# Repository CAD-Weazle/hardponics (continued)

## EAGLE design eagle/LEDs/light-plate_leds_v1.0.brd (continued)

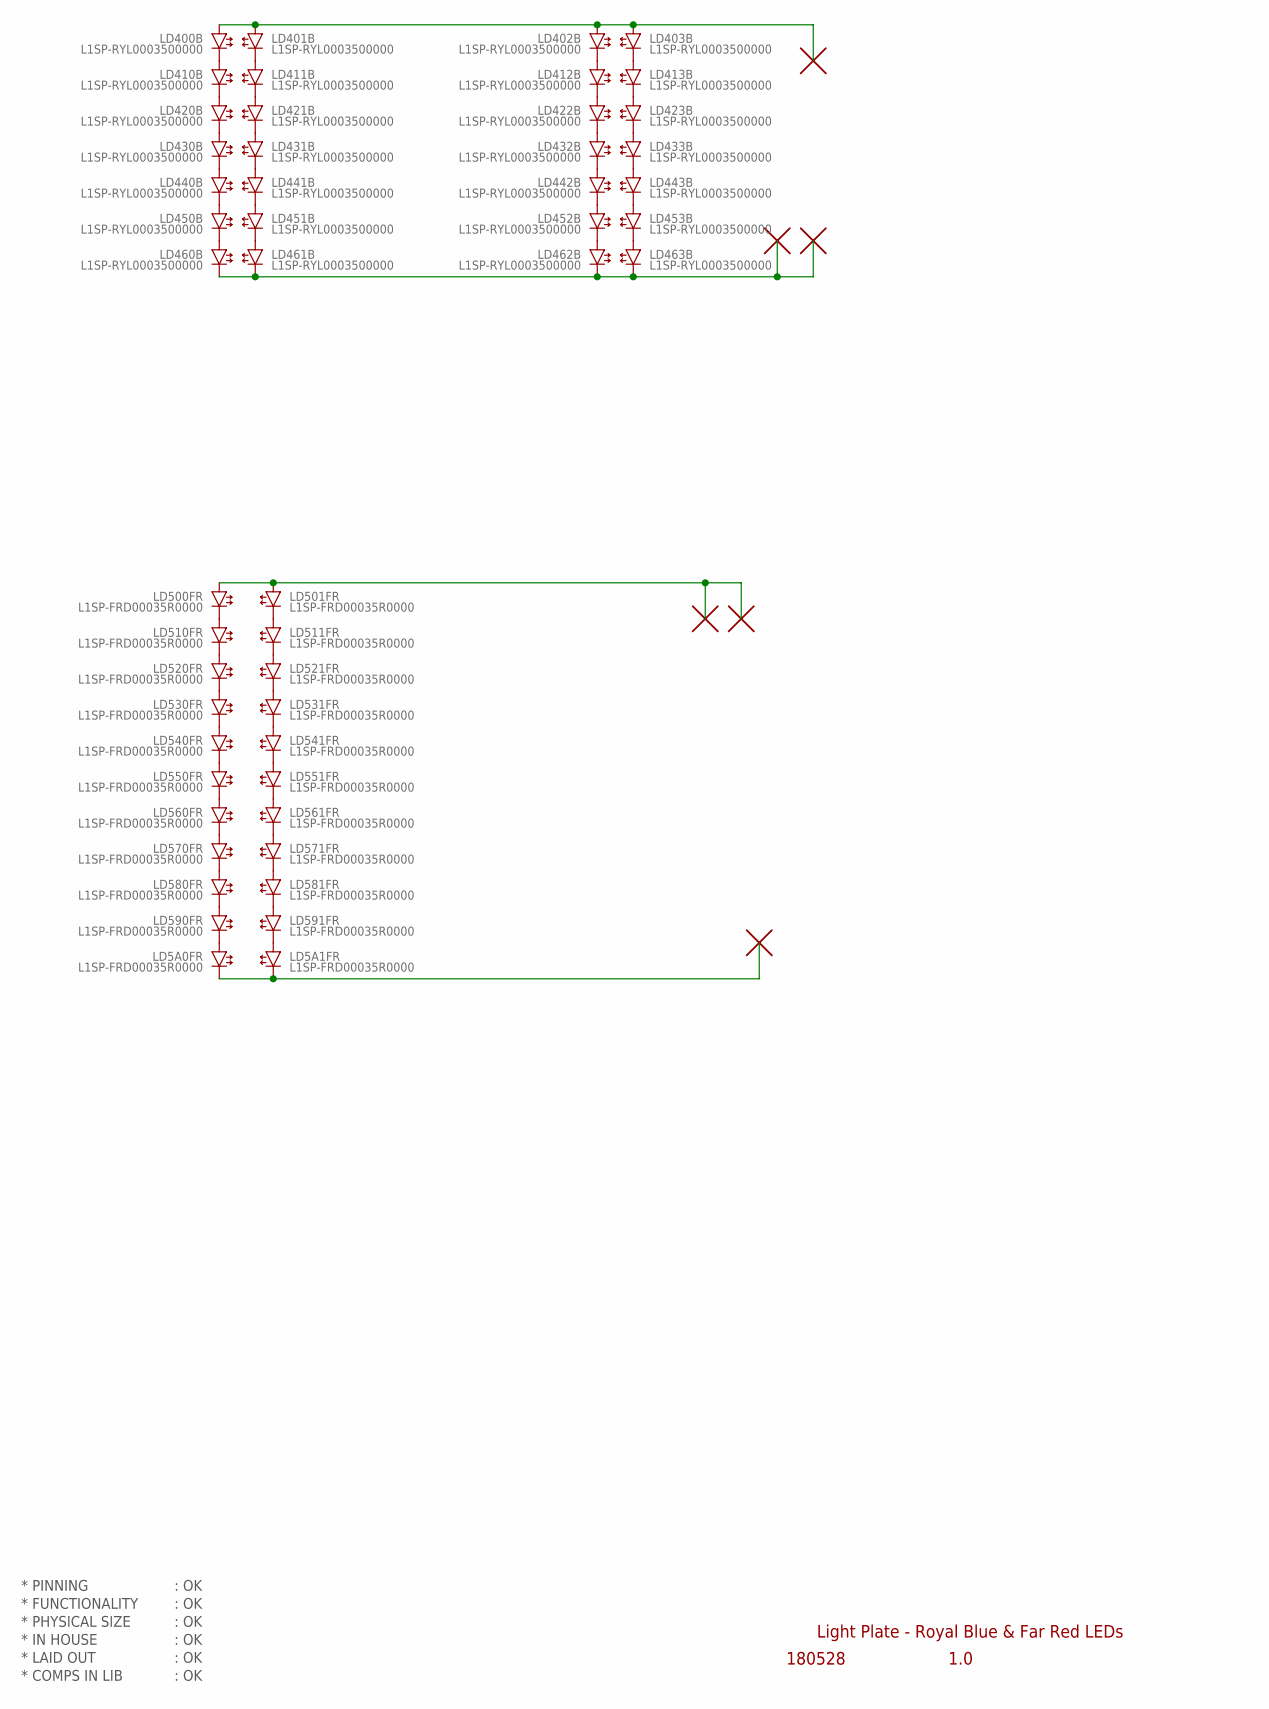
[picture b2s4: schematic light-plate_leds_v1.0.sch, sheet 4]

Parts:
H23, H24, H25, H26, H27, H28: PAD_ROUND_3.2MM
LD5A0FR, LD5A1FR, LD500FR, LD501FR, LD510FR, LD511FR, LD520FR, LD521FR, LD530FR, LD531FR, LD540FR, LD541FR, LD550FR, LD551FR, LD560FR, LD561FR, LD570FR, LD571FR, LD580FR, LD581FR, LD590FR, LD591FR: L1SP-FRD00035R0000; LED_SMD_SUNPLUS35_REVERSED
LD400B, LD401B, LD402B, LD403B, LD410B, LD411B, LD412B, LD413B, LD420B, LD421B, LD422B, LD423B, LD430B, LD431B, LD432B, LD433B, LD440B, LD441B, LD442B, LD443B, LD450B, LD451B, LD452B, LD453B, LD460B, LD461B, LD462B, LD463B: L1SP-RYL0003500000; LED_SMD_SUNPLUS35

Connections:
unnamed: LD402B.C (-), LD412B.A (+)
unnamed: LD412B.C (-), LD422B.A (+)
unnamed: LD422B.C (-), LD432B.A (+)
unnamed: LD432B.C (-), LD442B.A (+)
unnamed: LD442B.C (-), LD452B.A (+)
unnamed: LD452B.C (-), LD462B.A (+)
unnamed: LD403B.C (-), LD413B.A (+)
unnamed: LD413B.C (-), LD423B.A (+)
unnamed: LD423B.C (-), LD433B.A (+)
unnamed: LD433B.C (-), LD443B.A (+)
unnamed: H25.P, H27.P, LD500FR.C (+), LD501FR.C (+)
unnamed: LD443B.C (-), LD453B.A (+)
unnamed: LD453B.C (-), LD463B.A (+)
unnamed: LD400B.C (-), LD410B.A (+)
unnamed: LD410B.C (-), LD420B.A (+)
unnamed: LD420B.C (-), LD430B.A (+)
unnamed: LD430B.C (-), LD440B.A (+)
unnamed: LD440B.C (-), LD450B.A (+)
unnamed: LD450B.C (-), LD460B.A (+)
unnamed: LD401B.C (-), LD411B.A (+)
unnamed: LD411B.C (-), LD421B.A (+)
unnamed: LD421B.C (-), LD431B.A (+)
unnamed: LD431B.C (-), LD441B.A (+)
unnamed: LD441B.C (-), LD451B.A (+)
unnamed: LD451B.C (-), LD461B.A (+)
unnamed: LD500FR.A (-), LD510FR.C (+)
unnamed: LD510FR.A (-), LD520FR.C (+)
unnamed: LD520FR.A (-), LD530FR.C (+)
unnamed: LD530FR.A (-), LD540FR.C (+)
unnamed: LD540FR.A (-), LD550FR.C (+)
unnamed: LD550FR.A (-), LD560FR.C (+)
unnamed: LD560FR.A (-), LD570FR.C (+)
unnamed: LD570FR.A (-), LD580FR.C (+)
unnamed: LD580FR.A (-), LD590FR.C (+)
unnamed: LD5A0FR.C (+), LD590FR.A (-)
unnamed: LD501FR.A (-), LD511FR.C (+)
unnamed: LD511FR.A (-), LD521FR.C (+)
unnamed: LD521FR.A (-), LD531FR.C (+)
unnamed: LD531FR.A (-), LD541FR.C (+)
unnamed: LD541FR.A (-), LD551FR.C (+)
unnamed: LD551FR.A (-), LD561FR.C (+)
unnamed: LD561FR.A (-), LD571FR.C (+)
unnamed: LD571FR.A (-), LD581FR.C (+)
unnamed: LD581FR.A (-), LD591FR.C (+)
unnamed: LD5A1FR.C (+), LD591FR.A (-)
unnamed: H24.P, H28.P, LD460B.C (-), LD461B.C (-), LD462B.C (-), LD463B.C (-)
unnamed: H23.P, LD400B.A (+), LD401B.A (+), LD402B.A (+), LD403B.A (+)
unnamed: H26.P, LD5A0FR.A (-), LD5A1FR.A (-)

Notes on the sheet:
* PINNING
* FUNCTIONALITY
* PHYSICAL SIZE
* LAID OUT
* COMPS IN LIB
* IN HOUSE
: OK
Light Plate - Royal Blue & Far Red LEDs
1.0
180528

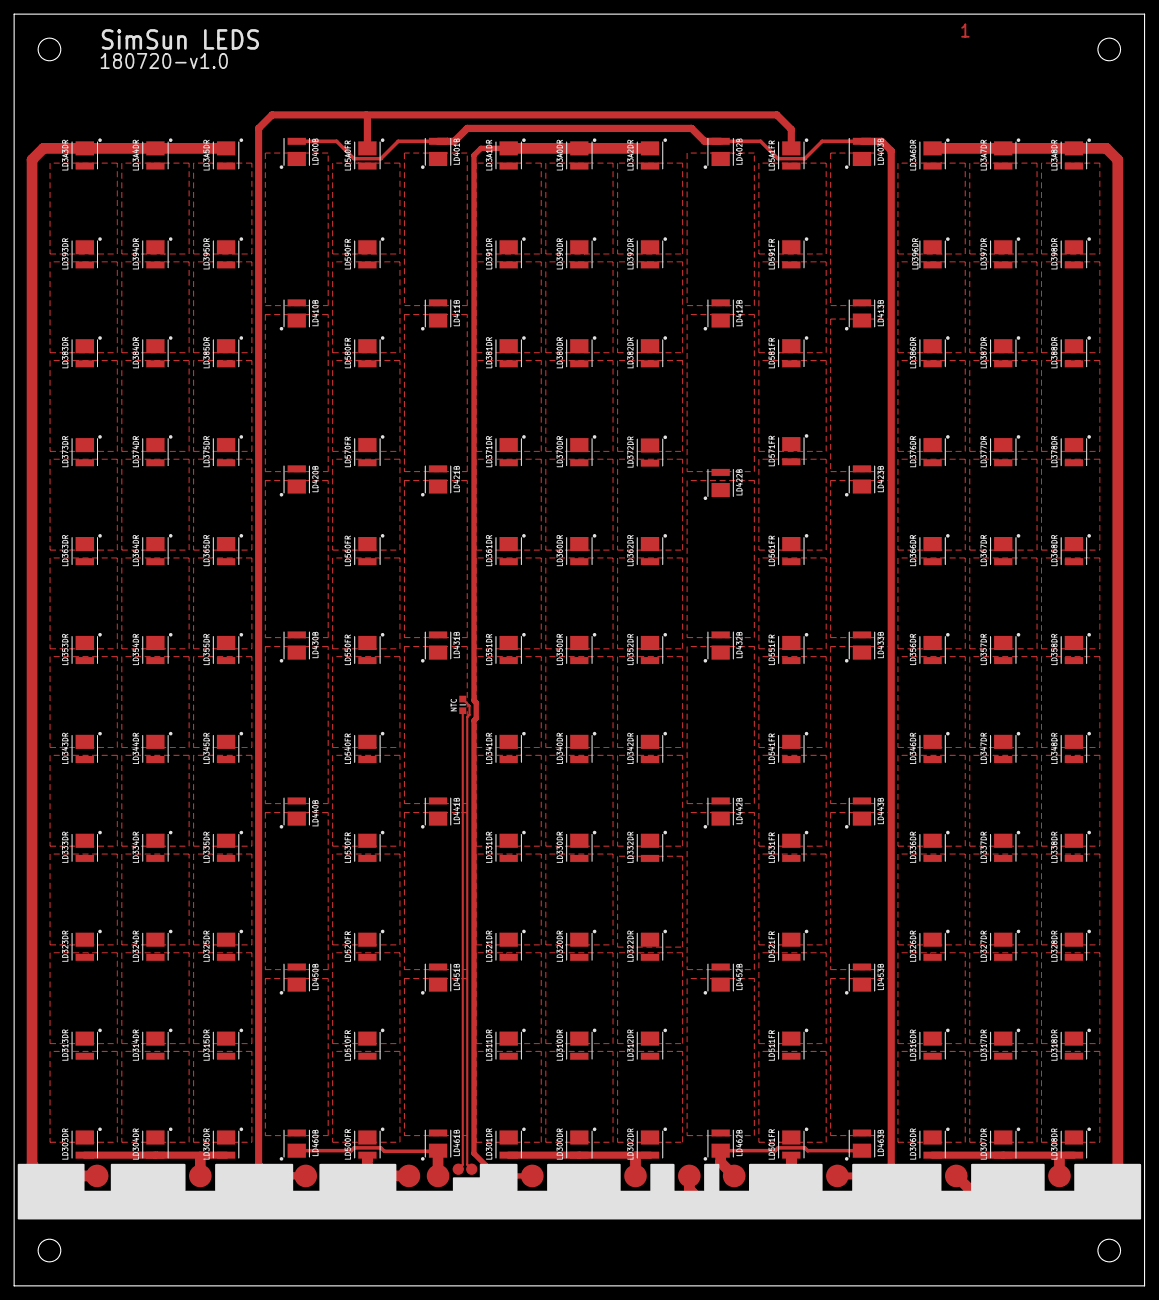
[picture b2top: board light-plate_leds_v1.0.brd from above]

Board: 2 copper layers, 160.0 x 180.0 mm, 168 parts (0 on the bottom side), 146 nets.

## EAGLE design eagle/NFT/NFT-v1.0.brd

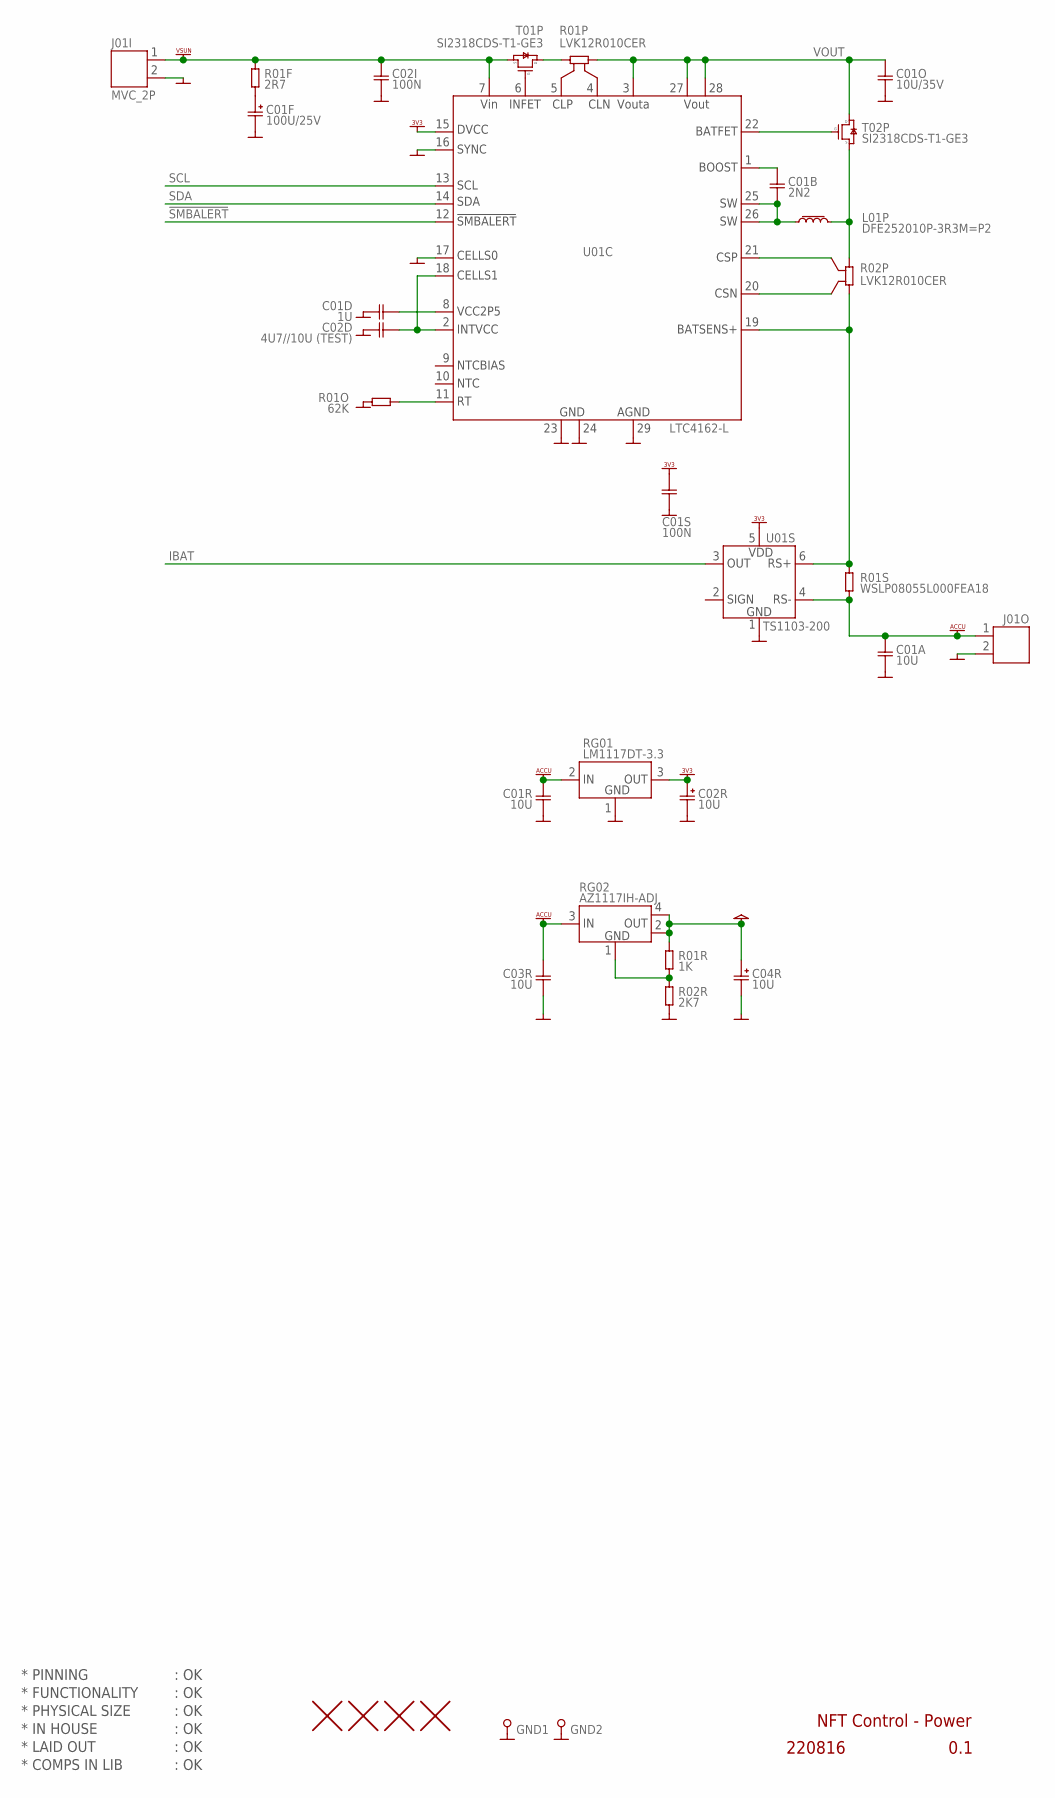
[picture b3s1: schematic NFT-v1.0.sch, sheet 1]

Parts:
C01A: 10U; CAP0805
C01B: 2N2; CAP0402
C01D: 1U; CAP0402
C01F: 100U/25V; ECAP_SMD
C01O: 10U/35V; CAP0805
C01R, C03R: 10U; CAP0603
C01S, C02I: 100N; CAP0402
C02D: 4U7//10U (TEST); CAP0402
C02R, C04R: 10U; ECAP_SMA
GND1, GND2: PIN_TEST; HOLE_PTH_0.8MM
H1, H2, H3, H4: HOLE_NPTH_3.2MM
J01I: MVC_2P; CON_PHOENIX_COMBICON_MCV_HEADER_P
J01O: CON_PHOENIX_COMBICON_MCV_HEADER_2P; CON_PHOENIX_COMBICON_MCV_HEADER_P
L01P: DFE252010P-3R3M=P2; L_1008
R01F: 2R7; RES0603
R01O: 62K; RES0402
R01P, R02P: LVK12R010CER; RES1206_LVK12R010CER
R01R: 1K; RES0402
R01S: WSLP08055L000FEA18; RES0805
R02R: 2K7; RES0402
RG01: LM1117DT-3.3; TO252
RG02: AZ1117IH-ADJ; SOT223
T01P, T02P: SI2318CDS-T1-GE3; NFET_SOT23
U01C: LTC4162-L; QFN28_4X5
U01S: TS1103-200; SOT23-6

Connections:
!SMBALERT: U01C.12 (12.!SMBALERT); also elsewhere on the board
ACCU: C01A.1, C01R.1, C03R.1, J01O.1, R01S.2, RG01.2 (2.IN), RG02.3 (3.IN), U01S.4 (4.RS-); also elsewhere on the board
BATFET: T02P.G (G1), U01C.22 (22.BATFET)
BOOST: C01B.1, U01C.1 (1.BOOST)
CHARGER_OUT: R01S.1, R02P.1, U01C.19 (19.BATSENS+), U01S.6 (6.RS+)
CLN: R01P.4, U01C.4 (4.CLN)
CLP: R01P.3, U01C.5 (5.CLP)
CSN: R02P.3, U01C.20 (20.CSN)
CSP: R02P.4, U01C.21 (21.CSP)
FB1: R01R.2, R02R.1, RG02.1 (1.GND)
GND: C01A.2, C01D.1, C01F.-, C01O.2, C01R.2, C01S.2, C02D.1, C02I.2, C02R.-, C03R.2, C04R.-, GND1.1, GND2.1, J01I.2, J01O.2, R01O.1, R02R.2, RG01.1 (1.GND), U01C.16 (16.SYNC), U01C.17 (17.CELLS0), U01C.23 (23.GND), U01C.24 (24.GND), U01C.29 (29.AGND), U01C.V1 (29.AGND), U01C.V2 (29.AGND), U01C.V3 (29.AGND), U01C.V4 (29.AGND), U01S.1 (1.GND); also elsewhere on the board
IBAT: U01S.3 (3.OUT); also elsewhere on the board
INFET: T01P.G (G1), U01C.6 (6.INFET)
INTVCC: C02D.2, U01C.2 (2.INTVCC), U01C.18 (18.CELLS1)
unnamed: C01F.+, R01F.2
unnamed: R01P.1, T01P.D (D3)
unnamed: L01P.2, R02P.2, T02P.S (S2)
RT: R01O.2, U01C.11 (11.RT)
SCL: U01C.13 (13.SCL); also elsewhere on the board
SDA: U01C.14 (14.SDA); also elsewhere on the board
SW: C01B.2, L01P.1, U01C.25 (25.SW), U01C.26 (26.SW)
VCC: C04R.+, R01R.1, RG02.2 (2.OUT), RG02.4 (4.OUT); also elsewhere on the board
VCC2P5: C01D.2, U01C.8 (8.VCC2P5)
VDD_3V3: C01S.1, C02R.+, RG01.3 (3.OUT), U01C.15 (15.DVCC), U01S.5 (5.VDD); also elsewhere on the board
VOUT: C01O.1, R01P.2, T02P.D (D3), U01C.3 (3.VOUTA), U01C.27 (27.VOUT), U01C.28 (28.VOUT)
VSUN: C02I.1, J01I.1, R01F.1, T01P.S (S2), U01C.7 (7.VIN)

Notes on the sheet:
* PINNING
* FUNCTIONALITY
* PHYSICAL SIZE
* LAID OUT
* COMPS IN LIB
* IN HOUSE
NFT Control - Power
220816
0.1
: OK

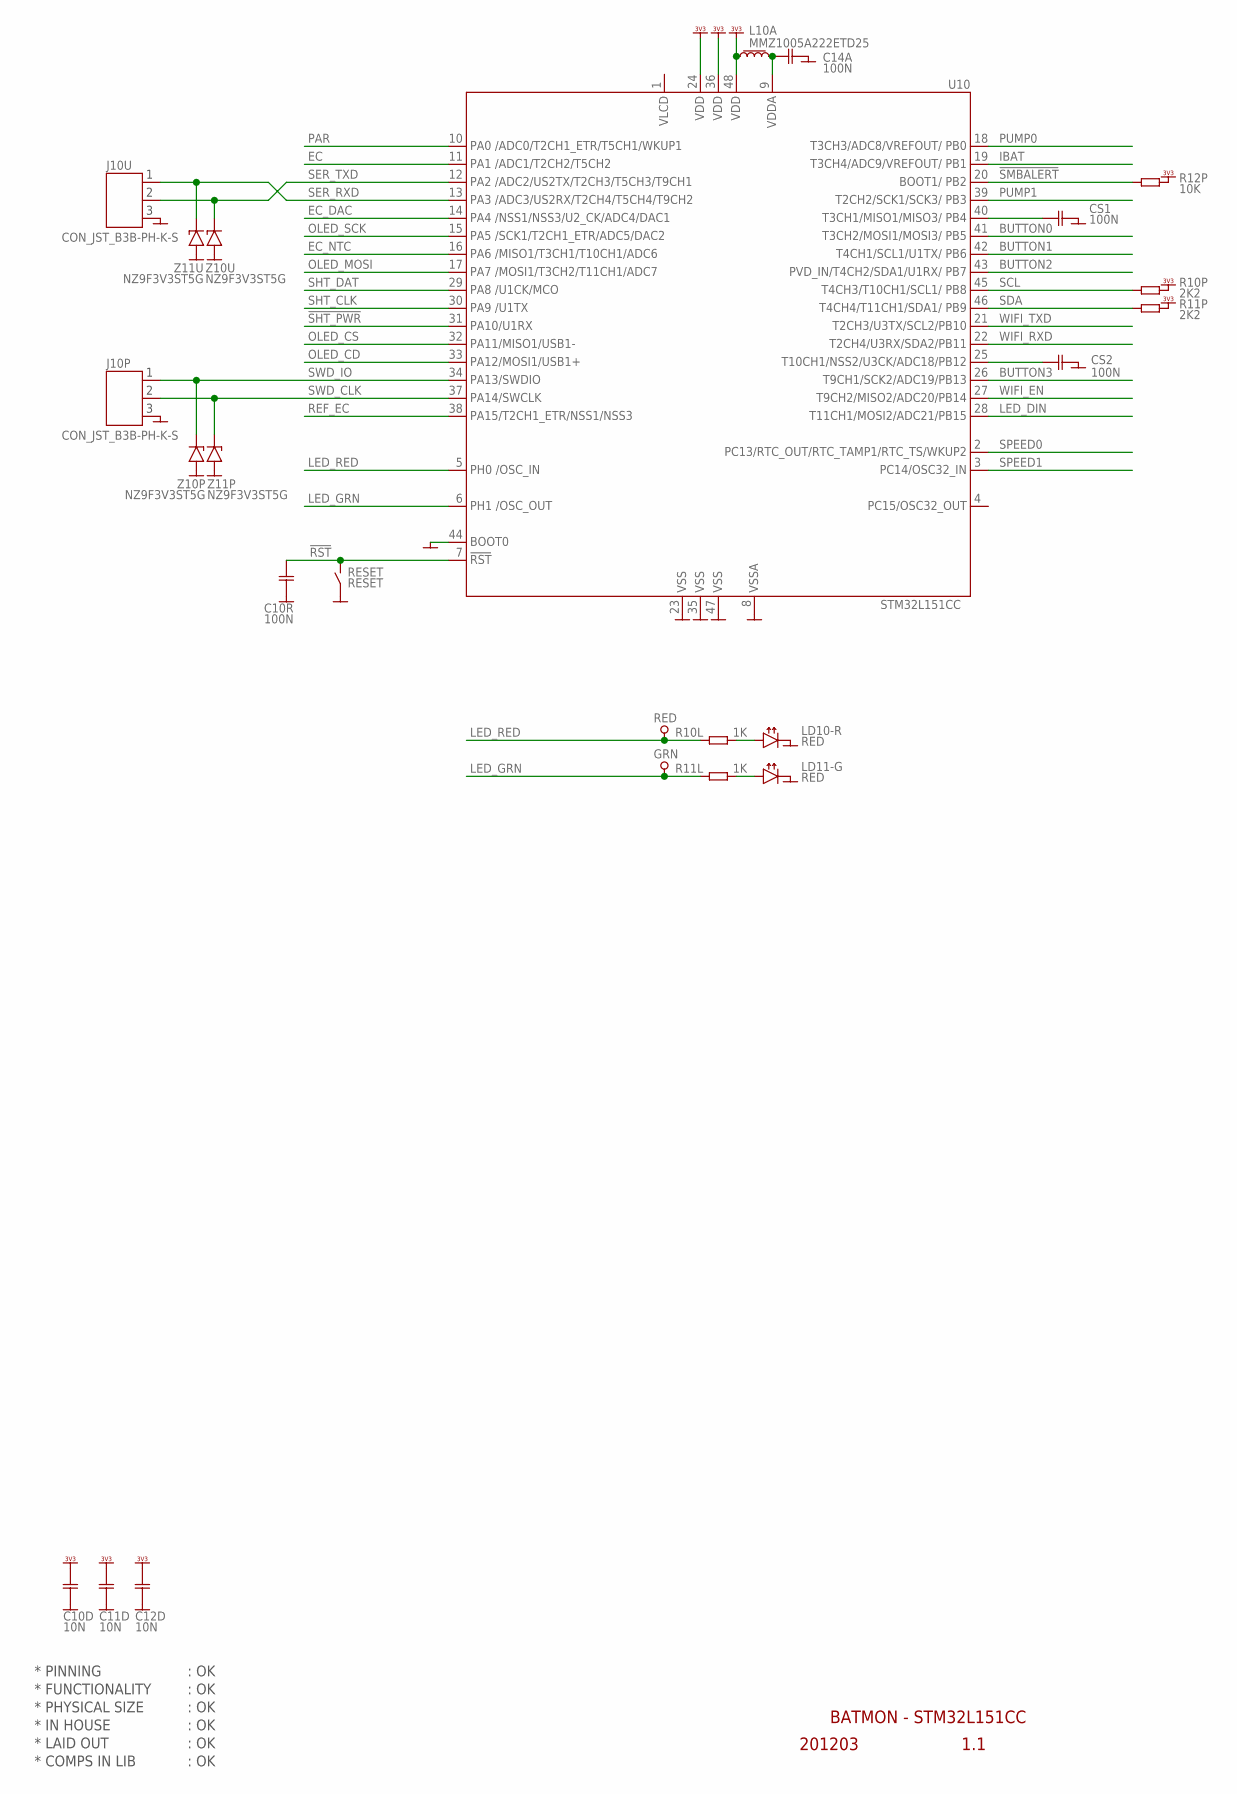
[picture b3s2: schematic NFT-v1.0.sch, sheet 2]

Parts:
C10D, C11D, C12D: 10N; CAP0402
C10R, C14A: 100N; CAP0402
CS1, CS2: 100N; CAP0402
GRN: PIN_TEST_0.6MM; HOLE_PTH_0.6MM
J10P, J10U: CON_JST_B3B-PH-K-S
L10A: MMZ1005A222ETD25; L_0402
LD10-R, LD11-G: RED; LED_SMD_0402
R10L, R11L: 1K; RES0402
R10P, R11P: 2K2; RES0402
R12P: 10K; RES0402
RED: PIN_TEST_0.6MM; HOLE_PTH_0.6MM
RESET: RESET; SWITCH_SMD_PBUTTON_2P
U10: STM32L151CC; LQFP48
Z10P, Z10U, Z11P, Z11U: NZ9F3V3ST5G; ZENER_SOD923

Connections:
!RST: C10R.1, RESET.1 (1-2), U10.7 (7.!RST)
!SHT_PWR: U10.31 (31.PA10); also elsewhere on the board
!SMBALERT: R12P.1, U10.20 (20.PB2); also elsewhere on the board
BUTTON0: U10.41 (41.PB5); also elsewhere on the board
BUTTON1: U10.42 (42.PB6); also elsewhere on the board
BUTTON2: U10.43 (43.PB7); also elsewhere on the board
BUTTON3: U10.26 (26.PB13); also elsewhere on the board
CSAMPLE: CS1.1, U10.40 (40.PB4)
CSAMPLE1: CS2.1, U10.25 (25.PB12)
EC: U10.11 (11.PA1); also elsewhere on the board
EC_DAC: U10.14 (14.PA4); also elsewhere on the board
EC_NTC: U10.16 (16.PA6); also elsewhere on the board
GND: C10D.2, C10R.2, C11D.2, C12D.2, C14A.2, CS1.2, CS2.2, J10P.3, J10U.3, LD10-R.C, LD11-G.C, RESET.2 (3-4), U10.8 (8.GND), U10.23 (23.GND), U10.35 (35.GND), U10.44 (44.BOOT0), U10.47 (47.GND), Z10P.2 (A), Z10U.2 (A), Z11P.2 (A), Z11U.2 (A); also elsewhere on the board
IBAT: U10.19 (19.PB1); also elsewhere on the board
LED_DIN: U10.28 (28.PB15); also elsewhere on the board
LED_GRN: GRN.1, R11L.1, U10.6 (6.OSC_OUT)
LED_RED: R10L.1, RED.1, U10.5 (5.OSC_IN)
unnamed: LD11-G.A, R11L.2
unnamed: LD10-R.A, R10L.2
OLED_CD: U10.33 (33.PA12); also elsewhere on the board
OLED_CS: U10.32 (32.PA11); also elsewhere on the board
OLED_MOSI: U10.17 (17.PA7); also elsewhere on the board
OLED_SCK: U10.15 (15.PA5); also elsewhere on the board
PAR: U10.10 (10.PA0); also elsewhere on the board
PUMP0: U10.18 (18.PB0); also elsewhere on the board
PUMP1: U10.39 (39.PB3); also elsewhere on the board
REF_EC: U10.38 (38.PA15); also elsewhere on the board
SCL: R10P.1, U10.45 (45.PB8); also elsewhere on the board
SDA: R11P.1, U10.46 (46.PB9); also elsewhere on the board
SER_RXD: J10U.1, U10.13 (13.PA3), Z11U.1 (C)
SER_TXD: J10U.2, U10.12 (12.PA2), Z10U.1 (C)
SHT_CLK: U10.30 (30.PA9); also elsewhere on the board
SHT_DAT: U10.29 (29.PA8); also elsewhere on the board
SPEED0: U10.2 (2.PC13); also elsewhere on the board
SPEED1: U10.3 (3.PC14); also elsewhere on the board
SWD_CLK: J10P.2, U10.37 (37.PA14), Z11P.1 (C)
SWD_IO: J10P.1, U10.34 (34.PA13), Z10P.1 (C)
VDDA: C14A.1, L10A.2, U10.9 (9.VDD)
VDD_3V3: C10D.1, C11D.1, C12D.1, L10A.1, R10P.2, R11P.2, R12P.2, U10.24 (24.VDD), U10.36 (36.VDD), U10.48 (48.VDD); also elsewhere on the board
WIFI_EN: U10.27 (27.PB14); also elsewhere on the board
WIFI_RXD: U10.22 (22.PB11); also elsewhere on the board
WIFI_TXD: U10.21 (21.PB10); also elsewhere on the board

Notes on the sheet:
* PINNING
* FUNCTIONALITY
* PHYSICAL SIZE
* LAID OUT
* COMPS IN LIB
* IN HOUSE
: OK
BATMON - STM32L151CC
201203
1.1

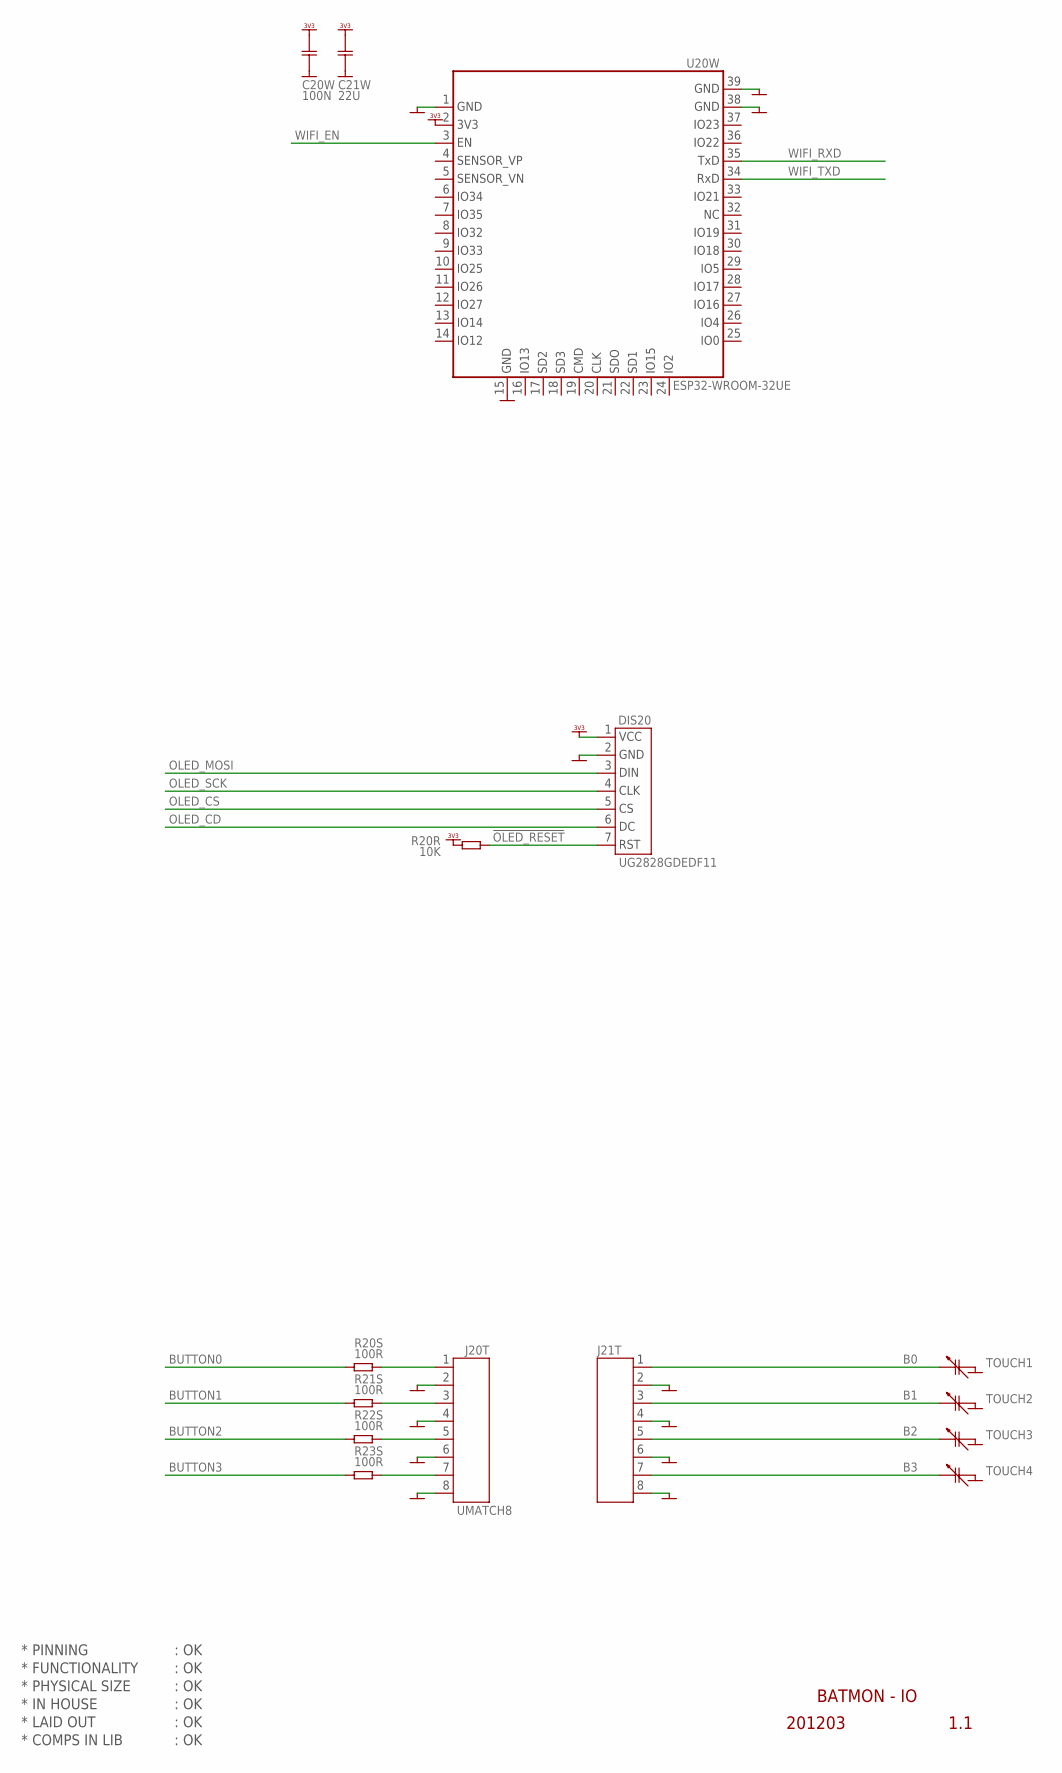
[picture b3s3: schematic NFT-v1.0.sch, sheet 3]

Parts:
C20W: 100N; CAP0402
C21W: 22U; CAP0805
DIS20: UG2828GDEDF11; WAVESHARE_1.5"OLED128X128
J20T: UMATCH8; CON_MICROMATCH_TOP_8F
J21T: CON_MICROMATCH_8F_SMD-TOP; CON_MICROMATCH_TOP_8F_SMD
R20R: 10K; RES0402
R20S, R21S, R22S, R23S: 100R; RES0402
TOUCH1, TOUCH2, TOUCH3, TOUCH4: CAP_TOUCH_ROUND_10MM_SINGLE
U20W: ESP32-WROOM-32UE

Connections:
!OLED_RESET: DIS20.7 (7.RST), R20R.2
B0: J20T.1, J21T.1, R20S.2, TOUCH1.1
B1: J20T.3, J21T.3, R21S.2, TOUCH2.1
B2: J20T.5, J21T.5, R22S.2, TOUCH3.1
B3: J20T.7, J21T.7, R23S.2, TOUCH4.1
BUTTON0: R20S.1; also elsewhere on the board
BUTTON1: R21S.1; also elsewhere on the board
BUTTON2: R22S.1; also elsewhere on the board
BUTTON3: R23S.1; also elsewhere on the board
GND: C20W.2, C21W.2, DIS20.2 (2.GND), J20T.2, J20T.4, J20T.6, J20T.8, J21T.2, J21T.4, J21T.6, J21T.8, TOUCH1.2, TOUCH2.2, TOUCH3.2, TOUCH4.2, U20W.1 (1.GND), U20W.15 (15.GND), U20W.38 (38.GND), U20W.GND (39.GND); also elsewhere on the board
OLED_CD: DIS20.6 (6.DC); also elsewhere on the board
OLED_CS: DIS20.5 (5.CS); also elsewhere on the board
OLED_MOSI: DIS20.3 (3.DIN); also elsewhere on the board
OLED_SCK: DIS20.4 (4.CLK); also elsewhere on the board
VDD_3V3: C20W.1, C21W.1, DIS20.1 (1.VCC), R20R.1, U20W.2 (2.3V3); also elsewhere on the board
WIFI_EN: U20W.3 (3.EN); also elsewhere on the board
WIFI_RXD: U20W.35 (35.TXD0); also elsewhere on the board
WIFI_TXD: U20W.34 (34.RXD0); also elsewhere on the board

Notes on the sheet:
* PINNING
* FUNCTIONALITY
* PHYSICAL SIZE
* LAID OUT
* COMPS IN LIB
* IN HOUSE
BATMON - IO
201203
1.1
: OK

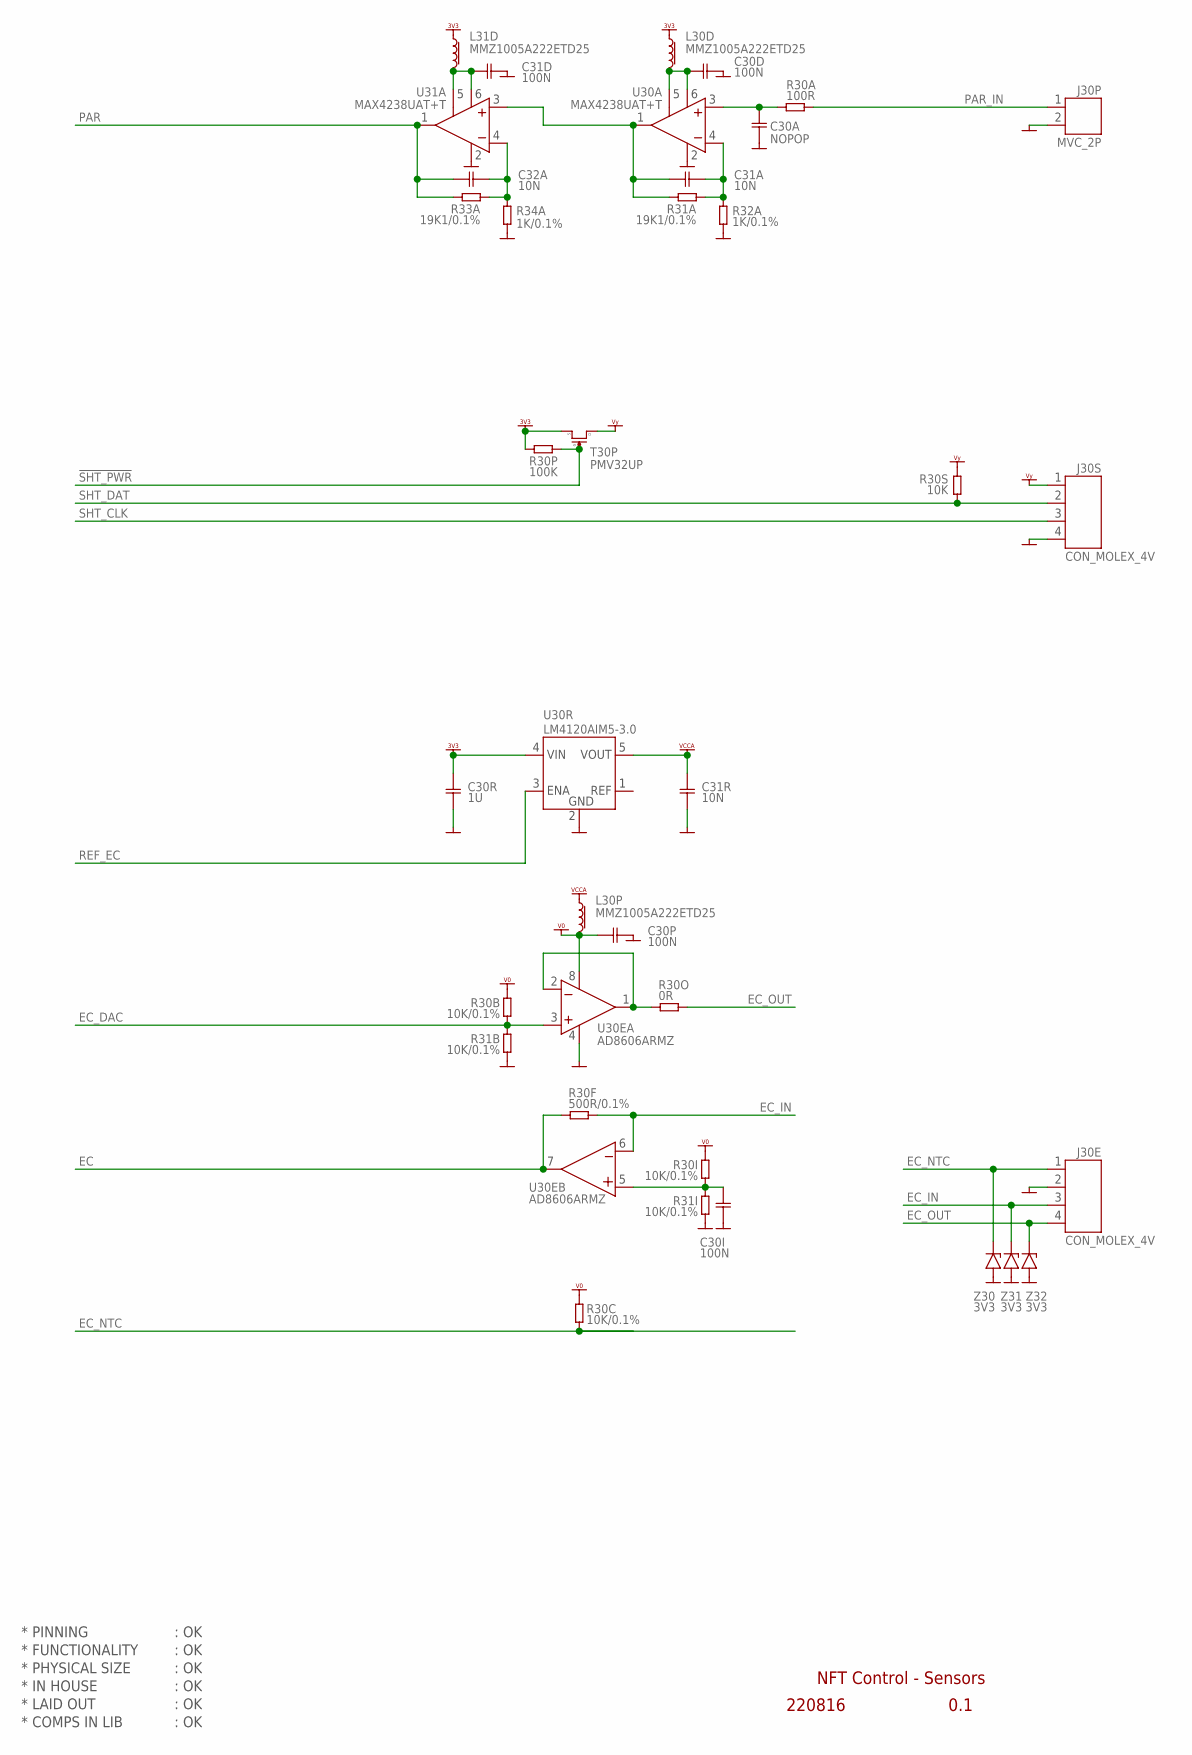
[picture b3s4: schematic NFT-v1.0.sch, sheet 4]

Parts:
C30A: NOPOP; CAP0402
C30D, C30I, C30P, C31D: 100N; CAP0402
C30R: 1U; CAP0402
C31A, C31R, C32A: 10N; CAP0402
J30E, J30S: CON_MOLEX_4V
J30P: MVC_2P; CON_PHOENIX_COMBICON_MCV_HEADER_P
L30D, L30P, L31D: MMZ1005A222ETD25; L_0402
R30A: 100R; RES0402
R30B, R30C, R30I, R31B, R31I: 10K/0.1%; RES0402
R30F: 500R/0.1%; RES0402
R30O: 0R; RES0402
R30P: 100K; RES0402
R30S: 10K; RES0402
R31A, R33A: 19K1/0.1%; RES0402
R32A, R34A: 1K/0.1%; RES0402
T30P: PMV32UP; PFET_SOT23
U30A, U31A: MAX4238UAT+T; SOT23-6
U30E: AD8606ARMZ; MSOP8
U30R: LM4120AIM5-3.0; SOT23-5
Z30, Z31, Z32: 3V3; ZENER_SOD80

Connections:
!SHT_PWR: R30P.2, T30P.1 (G); also elsewhere on the board
EC: R30F.2, U30E.7 (7.OUT); also elsewhere on the board
EC30_BUF: R30O.2, U30E.1 (1.OUT), U30E.2 (2.IN-)
EC_DAC: R30B.2, R31B.1, U30E.3 (3.IN+); also elsewhere on the board
EC_IN: J30E.3, R30F.1, U30E.6 (6.IN-), Z31.2 (C)
EC_NTC: J30E.1, R30C.2, Z30.2 (C); also elsewhere on the board
EC_OUT: J30E.4, R30O.1, Z32.2 (C)
GND: C30A.1, C30D.2, C30I.1, C30P.2, C30R.2, C31D.2, C31R.2, J30E.2, J30P.2, J30S.4, R31B.2, R31I.2, R32A.2, R34A.2, U30A.2 (2.V-), U30E.4 (4.V-), U30R.2 (2.GND), U31A.2 (2.V-), Z30.1 (A), Z31.1 (A), Z32.1 (A); also elsewhere on the board
IMUXF: C30A.2, R30A.2, U30A.3 (3.IN+)
unnamed: C31D.1, L31D.2, U31A.5 (5.!SHDN), U31A.6 (6.V+)
unnamed: C30I.2, R30I.2, R31I.1, U30E.5 (5.IN+)
unnamed: C30D.1, L30D.2, U30A.5 (5.!SHDN), U30A.6 (6.V+)
unnamed: C32A.2, R33A.1, R34A.1, U31A.4 (4.IN-)
unnamed: C31A.1, R31A.2, U30A.1 (1.OUT), U31A.3 (3.IN+)
unnamed: C31A.2, R31A.1, R32A.1, U30A.4 (4.IN-)
PAR: C32A.1, R33A.2, U31A.1 (1.OUT); also elsewhere on the board
PAR_IN: J30P.1, R30A.1
REF_EC: U30R.3 (3.ENA); also elsewhere on the board
SHT_CLK: J30S.3; also elsewhere on the board
SHT_DAT: J30S.2, R30S.2; also elsewhere on the board
V0: C30P.1, L30P.2, R30B.1, R30C.1, R30I.1, U30E.8 (8.V+)
VCCA: C31R.1, L30P.1, U30R.5 (5.VOUT)
VDD_3V3: C30R.1, L30D.1, L31D.1, R30P.1, T30P.2 (S), U30R.4 (4.VIN); also elsewhere on the board
VY: J30S.1, R30S.1, T30P.3 (D)

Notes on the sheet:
* PINNING
* FUNCTIONALITY
* PHYSICAL SIZE
* LAID OUT
* COMPS IN LIB
* IN HOUSE
NFT Control - Sensors
220816
0.1
: OK

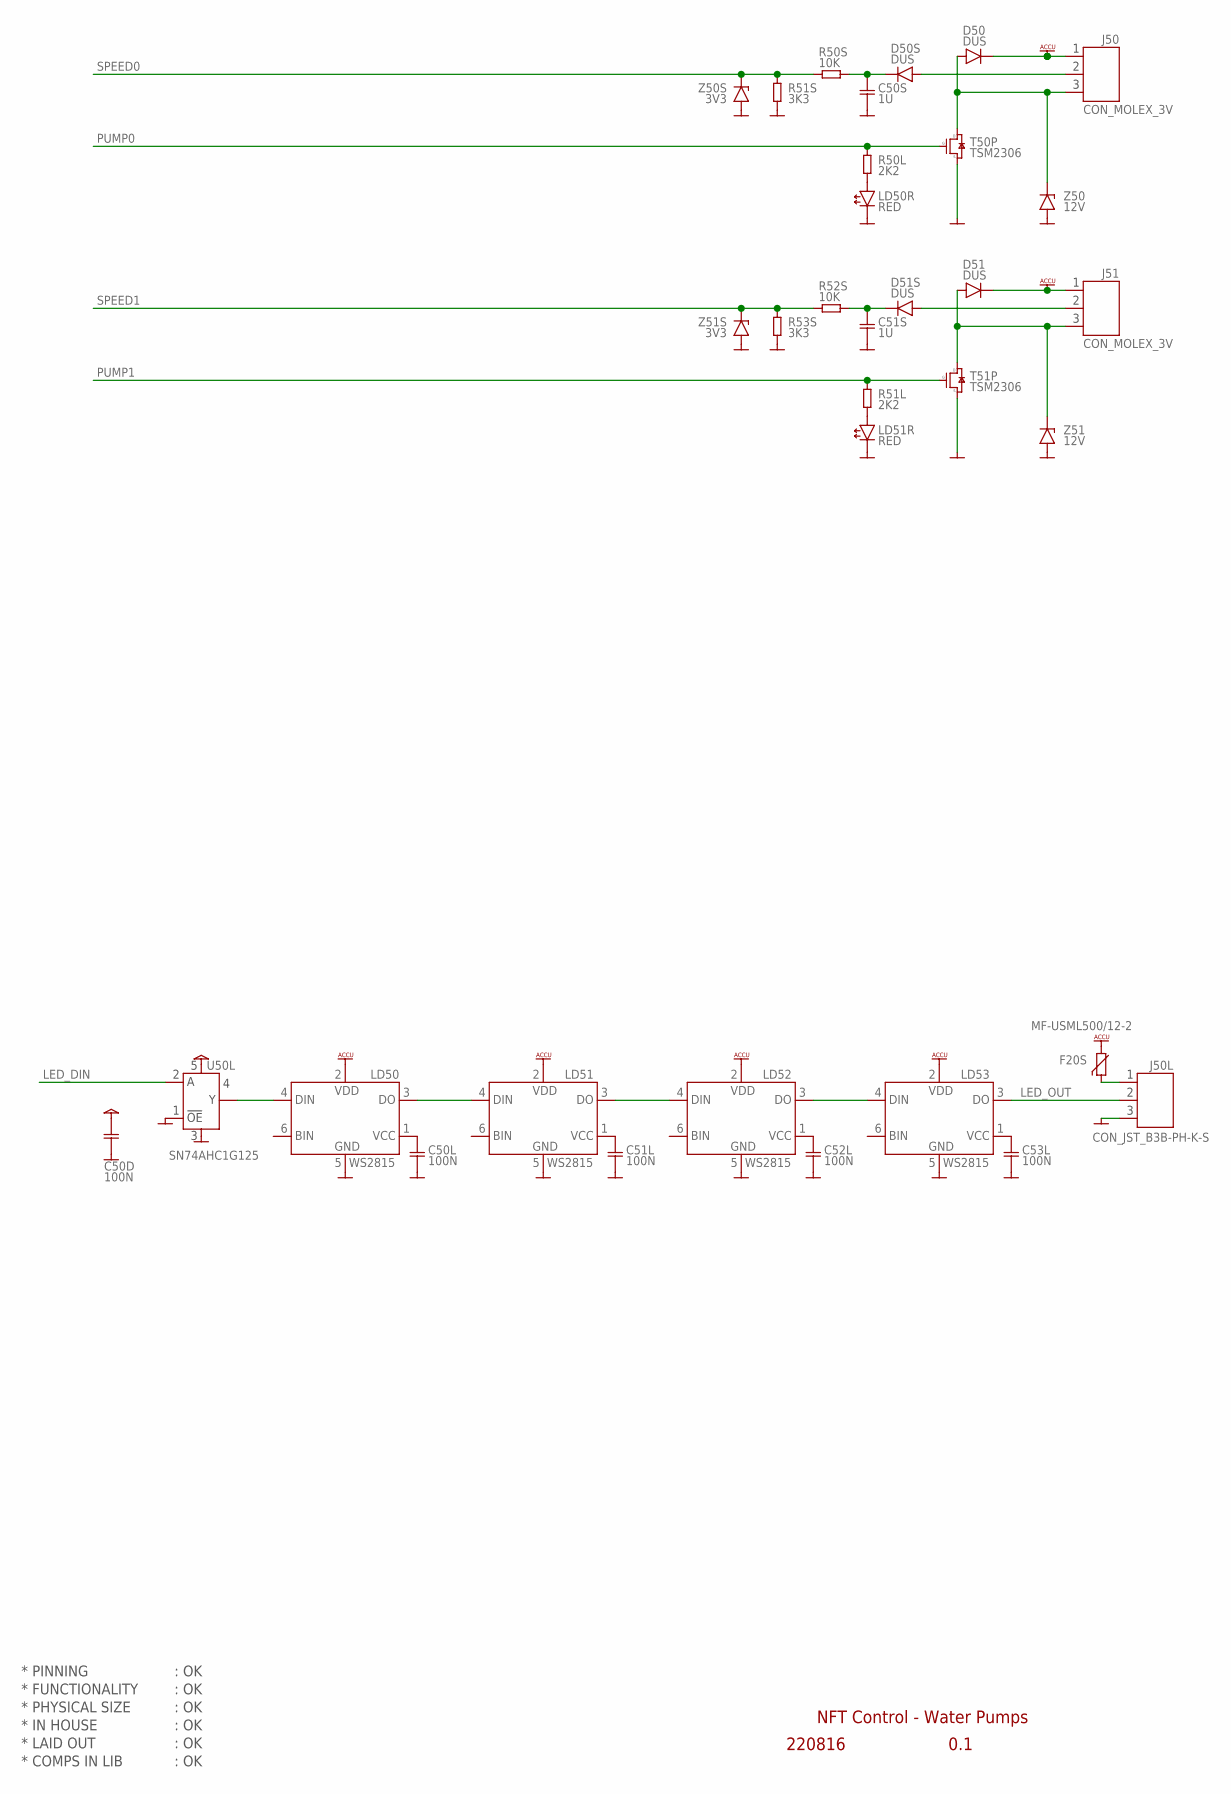
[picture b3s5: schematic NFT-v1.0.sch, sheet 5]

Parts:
C50D, C50L, C51L, C52L, C53L: 100N; CAP0402
C50S, C51S: 1U; CAP0402
D50, D50S, D51, D51S: DUS; DIODE_SOD323
F20S: MF-USML500/12-2; RES1210
J50, J51: CON_MOLEX_3V
J50L: CON_JST_B3B-PH-K-S
LD50, LD51, LD52, LD53: WS2815
LD50R, LD51R: RED; LED_SMD_0402
R50L, R51L: 2K2; RES0402
R50S, R52S: 10K; RES0402
R51S, R53S: 3K3; RES0402
T50P, T51P: TSM2306; NFET_SOT23
U50L: SN74AHC1G125; SOT553-5
Z50, Z51: 12V; ZENER_SOD80
Z50S, Z51S: 3V3; ZENER_SOD80

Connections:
ACCU: D50.1- (-), D51.1- (-), F20S.2, J50.1, J51.1, LD50.2 (2.VDD), LD51.2 (2.VDD), LD52.2 (2.VDD), LD53.2 (2.VDD); also elsewhere on the board
DI: LD50.4 (4.DIN), U50L.4 (4.Y)
GND: C50D.2, C50L.2, C50S.2, C51L.2, C51S.2, C52L.2, C53L.2, J50L.3, LD50.5 (5.GND), LD50R.C, LD51.5 (5.GND), LD51R.C, LD52.5 (5.GND), LD53.5 (5.GND), R51S.2, R53S.2, T50P.S (S2), T51P.S (S2), U50L.1 (1.OE), U50L.3 (3.GND), Z50.1 (A), Z50S.1 (A), Z51.1 (A), Z51S.1 (A); also elsewhere on the board
LED_DIN: U50L.2 (2.A); also elsewhere on the board
LED_OUT: J50L.2, LD53.3 (3.DO)
unnamed: C50L.1, LD50.1 (1.VCC)
unnamed: C51L.1, LD51.1 (1.VCC)
unnamed: C52L.1, LD52.1 (1.VCC)
unnamed: C53L.1, LD53.1 (1.VCC)
unnamed: LD51R.A, R51L.2
unnamed: C50S.1, D50S.1- (-), R50S.2
unnamed: C51S.1, D51S.1- (-), R52S.2
unnamed: F20S.1, J50L.1
unnamed: LD50R.A, R50L.2
P0: D50.2 (+), J50.3, T50P.D (D3), Z50.2 (C)
P1: D51.2 (+), J51.3, T51P.D (D3), Z51.2 (C)
PUMP0: R50L.1, T50P.G (G1); also elsewhere on the board
PUMP1: R51L.1, T51P.G (G1); also elsewhere on the board
S0: D50S.2 (+), J50.2
S1: D51S.2 (+), J51.2
SPEED0: R50S.1, R51S.1, Z50S.2 (C); also elsewhere on the board
SPEED1: R52S.1, R53S.1, Z51S.2 (C); also elsewhere on the board
VCC: C50D.1, U50L.5 (5.VDD); also elsewhere on the board
X0: LD50.3 (3.DO), LD51.4 (4.DIN)
X1: LD51.3 (3.DO), LD52.4 (4.DIN)
X2: LD52.3 (3.DO), LD53.4 (4.DIN)

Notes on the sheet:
* PINNING
* FUNCTIONALITY
* PHYSICAL SIZE
* LAID OUT
* COMPS IN LIB
* IN HOUSE
NFT Control - Water Pumps
220816
0.1
: OK
